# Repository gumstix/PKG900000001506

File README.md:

# Gumstix Raspberry Pi CM Robo
## PKG900000001506 ![][thumbnail]

**The Gumstix Raspberry Pi CM Robo** carrier board is a slim, computer vision-capable multimedia platform designed with miniature autonomous vehicles in mind.  The dual Raspberry Pi Camera connectors can provide either stereoscopic depth mapping for object avoidance or front- and back-facing cameras for feature identification or manual control.

I2C and UART serial connections, exposed via JST GH-style headers, can be used to connect either to PWM motor controller boards, or to a control MCU.

Instantly upgrade your project with the Gumstix Raspberry Pi CM4 Uprev board and take advantage of the CM4's increased horsepower.  Or go even further with the UprevAI and add a Google Coral TPU for lightning-fast TensorFlow processing.

__Features Include__:
* Power via **USB Type-C Power Delivery**
* Mini-HDMI-out
* DSI touch display connector
* Dual CSI2 camera connectors
* USB Type-A host connection
* 2x WS2812B-MINI RGB LEDs

__Links:__
* [AutoDoc Datasheet][autodoc]
* [Specifications][spec]
* [Store Page][store]
* [Schematics and Layout][hardware]

[thumbnail]: https://d3iwea566ns1n1.cloudfront.net/images/product/cfc476a8175b0227c75bd2853a3e6107ad4b8505.png
[autodoc]: PKG900000001506_AutoDoc.pdf
[spec]: PKG900000001506_SpecSheet.pdf
[store]: https://store.gumstix.com/cm-robo/
[hardware]: hardware/hardware.md
[firmware]: firmware/firmware.md

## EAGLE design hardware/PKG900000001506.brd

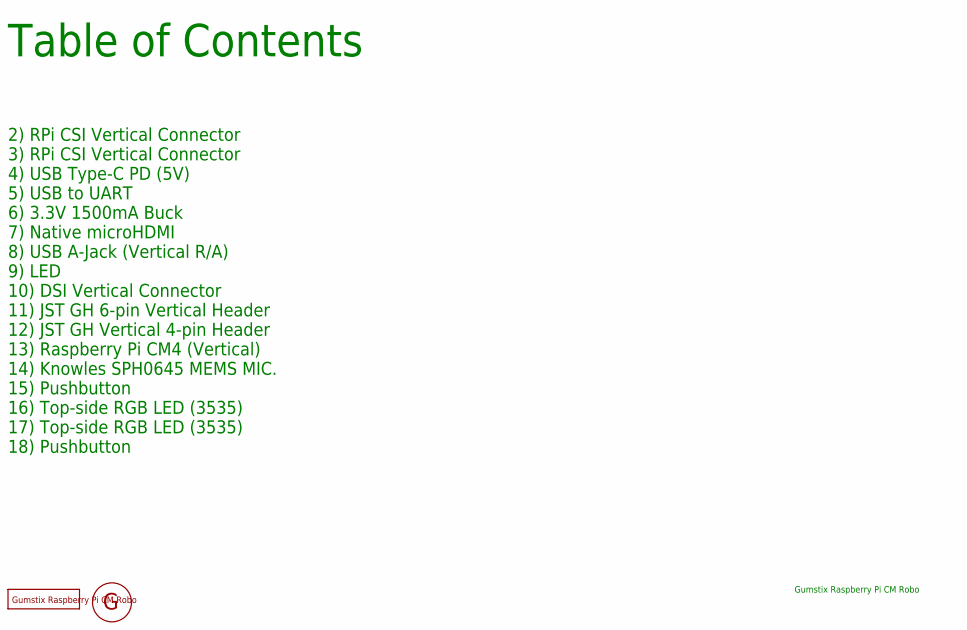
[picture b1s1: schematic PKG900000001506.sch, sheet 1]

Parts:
FD1, FD2, FD3, FD4, FD5, FD6, FD7, FD8: DNP; FIDUCIAL
U$4: DNP; GEPPETTO_LABEL
U$5: DNP; GEPPETTO_LOGO_SILK10

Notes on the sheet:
Table of Contents
Gumstix Raspberry Pi CM Robo
2) RPi CSI Vertical Connector
3) RPi CSI Vertical Connector
4) USB Type-C PD (5V)
5) USB to UART
6) 3.3V 1500mA Buck
7) Native microHDMI
8) USB A-Jack (Vertical R/A)
9) LED
10) DSI Vertical Connector
11) JST GH 6-pin Vertical Header
12) JST GH Vertical 4-pin Header
13) Raspberry Pi CM4 (Vertical)
14) Knowles SPH0645 MEMS MIC.
15) Pushbutton
16) Top-side RGB LED (3535)
17) Top-side RGB LED (3535)
18) Pushbutton

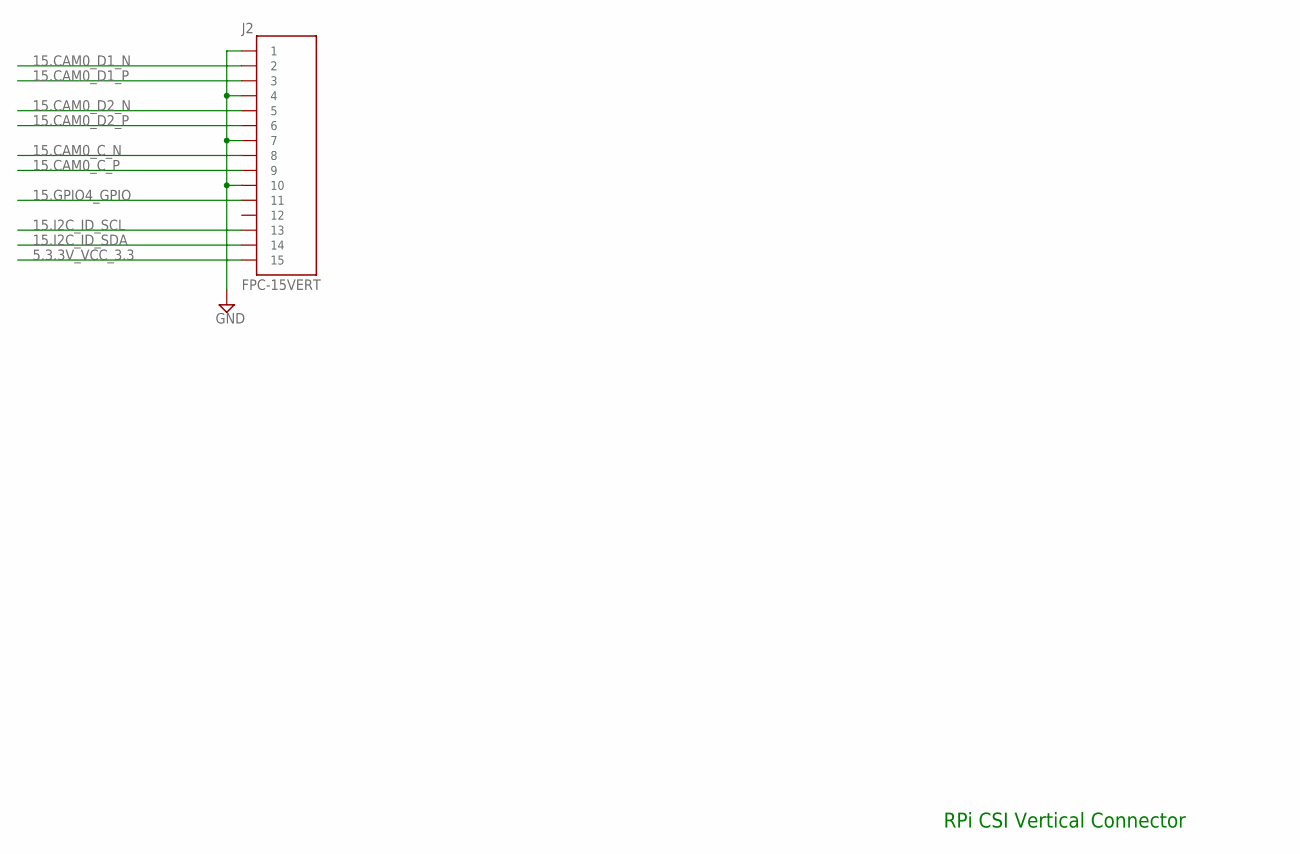
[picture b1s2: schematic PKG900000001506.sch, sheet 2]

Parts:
J2: FPC-15VERT; 1-1734248-5

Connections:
5.3.3V_VCC_3.3: J2.1_15 (15); also elsewhere on the board
15.CAM0_C_N: J2.1_8 (8); also elsewhere on the board
15.CAM0_C_P: J2.1_9 (9); also elsewhere on the board
15.CAM0_D1_N: J2.1_2 (2); also elsewhere on the board
15.CAM0_D1_P: J2.1_3 (3); also elsewhere on the board
15.CAM0_D2_N: J2.1_5 (5); also elsewhere on the board
15.CAM0_D2_P: J2.1_6 (6); also elsewhere on the board
15.GPIO4_GPIO: J2.1_11 (11); also elsewhere on the board
15.I2C_ID_SCL: J2.1_13 (13); also elsewhere on the board
15.I2C_ID_SDA: J2.1_14 (14); also elsewhere on the board
GND: J2.1_1 (1), J2.1_4 (4), J2.1_7 (7), J2.1_10 (10); also elsewhere on the board

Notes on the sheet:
RPi CSI Vertical Connector

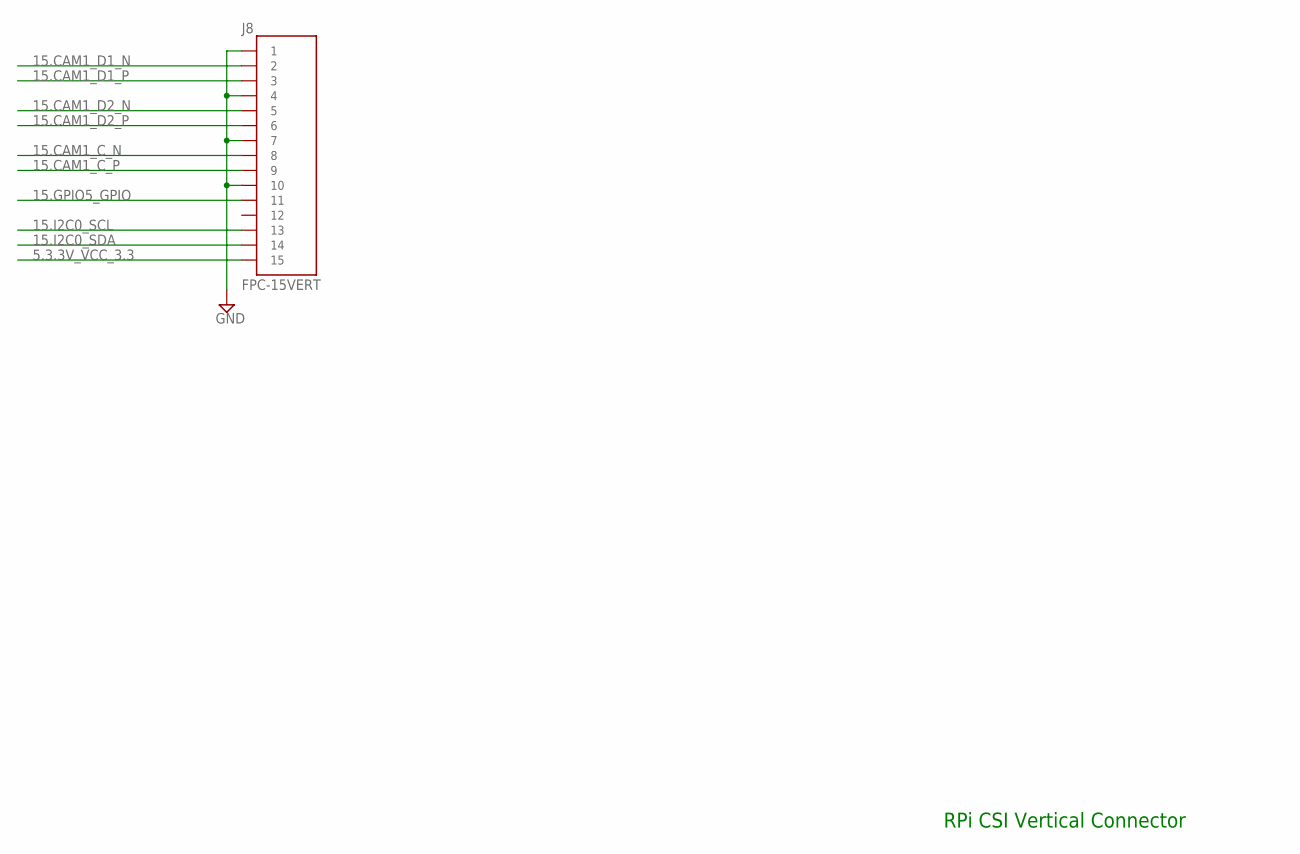
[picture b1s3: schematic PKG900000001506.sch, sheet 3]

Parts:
J8: FPC-15VERT; 1-1734248-5

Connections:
5.3.3V_VCC_3.3: J8.1_15 (15); also elsewhere on the board
15.CAM1_C_N: J8.1_8 (8); also elsewhere on the board
15.CAM1_C_P: J8.1_9 (9); also elsewhere on the board
15.CAM1_D1_N: J8.1_2 (2); also elsewhere on the board
15.CAM1_D1_P: J8.1_3 (3); also elsewhere on the board
15.CAM1_D2_N: J8.1_5 (5); also elsewhere on the board
15.CAM1_D2_P: J8.1_6 (6); also elsewhere on the board
15.GPIO5_GPIO: J8.1_11 (11); also elsewhere on the board
15.I2C0_SCL: J8.1_13 (13); also elsewhere on the board
15.I2C0_SDA: J8.1_14 (14); also elsewhere on the board
GND: J8.1_1 (1), J8.1_4 (4), J8.1_7 (7), J8.1_10 (10); also elsewhere on the board

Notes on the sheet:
RPi CSI Vertical Connector

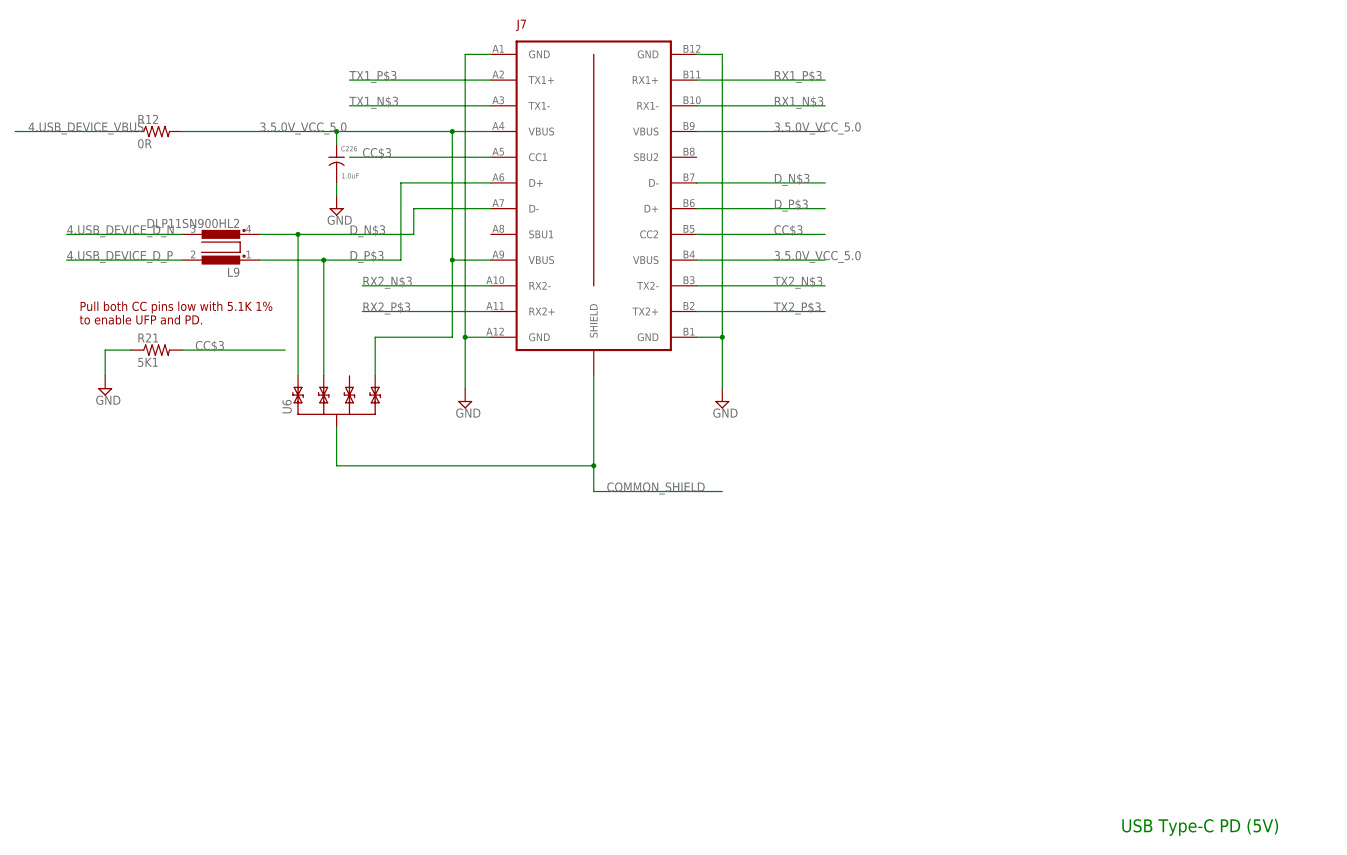
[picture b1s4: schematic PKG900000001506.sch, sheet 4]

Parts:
C226: 1.0uF; 0402
J7: USB-TYPE-C; USB-TYPE-C-SMT
L9: DLP11SN900HL2; 0504-DLP11S
R12: 0R; 0201
R21: 5K1; 0201
U6: TPD4E02B0410-USON; UFDFN-10

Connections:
3.5.0V_VCC_5.0: C226.1, J7.A4 (VBUS), J7.A9 (VBUS), J7.B4 (VBUS), J7.B9 (VBUS), R12.2, U6.5 (P4), U6.6 (P4); also elsewhere on the board
4.USB_DEVICE_D_N: L9.3; also elsewhere on the board
4.USB_DEVICE_D_P: L9.2; also elsewhere on the board
4.USB_DEVICE_VBUS: R12.1; also elsewhere on the board
CC$3: J7.A5 (CC1), J7.B5 (CC2), R21.2
COMMON_SHIELD: J7.P$1 (SHIELD), J7.P$2 (SHIELD), J7.P$3 (SHIELD), J7.P$4 (SHIELD), U6.3 (SHIELD), U6.8 (SHIELD); also elsewhere on the board
D_N$3: J7.A7 (D-), J7.B7 (D-), L9.4, U6.1, U6.10 (P1)
D_P$3: J7.A6 (D+), J7.B6 (D+), L9.1, U6.2, U6.9 (P2)
GND: C226.2, J7.A1 (GND), J7.A12 (GND), J7.B1 (GND), J7.B12 (GND), R21.1; also elsewhere on the board
RX1_N$3: J7.B10 (RX1-)
RX1_P$3: J7.B11 (RX1+)
RX2_N$3: J7.A10 (RX2-)
RX2_P$3: J7.A11 (RX2+)
TX1_N$3: J7.A3 (TX1-)
TX1_P$3: J7.A2 (TX1+)
TX2_N$3: J7.B3 (TX2-)
TX2_P$3: J7.B2 (TX2+)

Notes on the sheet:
USB Type-C PD (5V)
Pull both CC pins low with 5.1K 1% to enable UFP and PD.

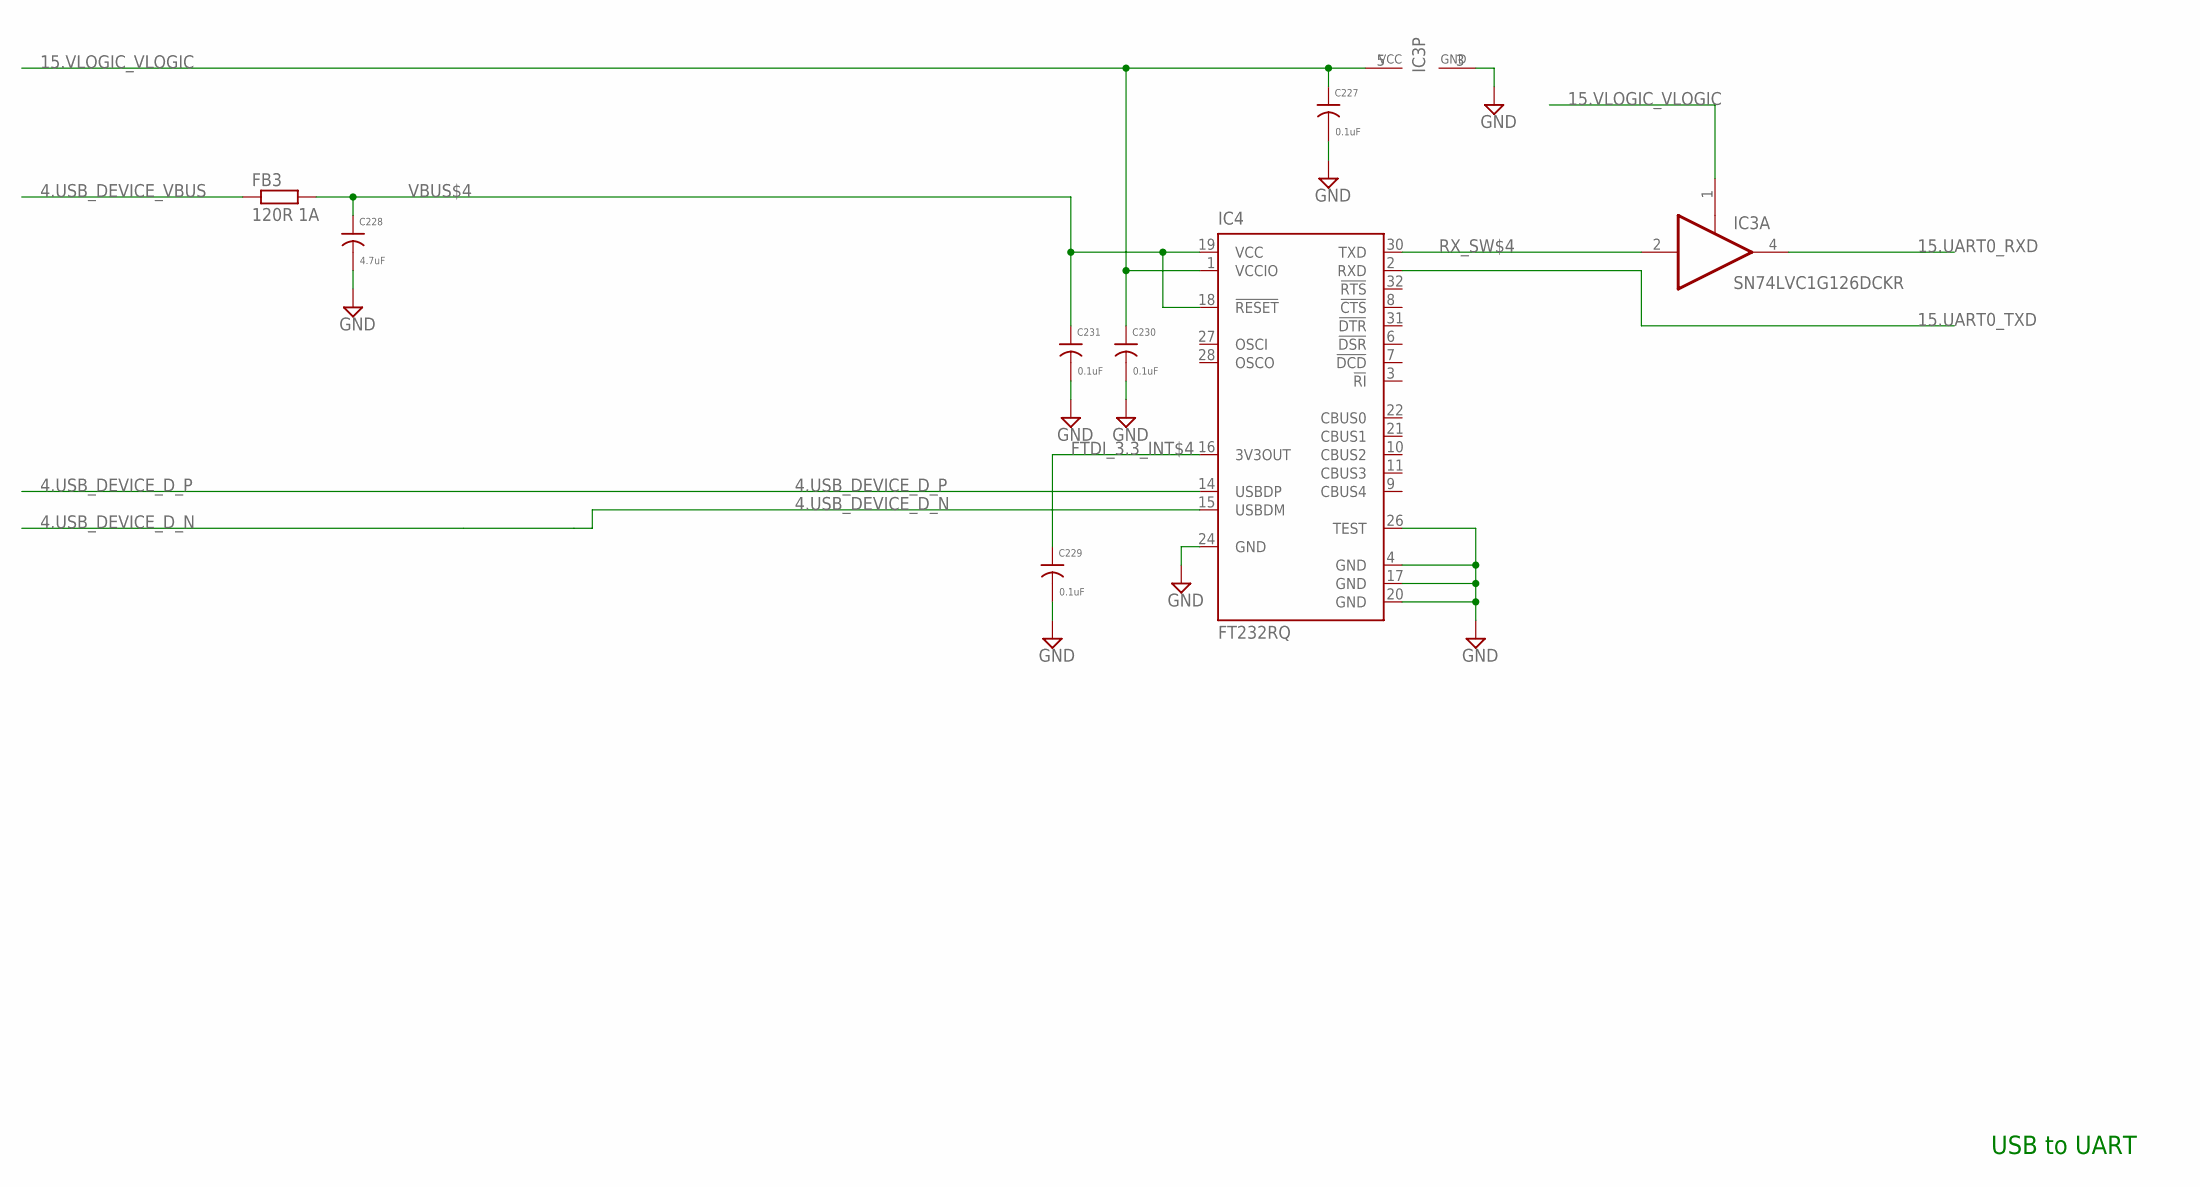
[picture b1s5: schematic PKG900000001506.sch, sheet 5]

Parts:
C227, C229, C230, C231: 0.1uF; 0201
C228: 4.7uF; 0603
FB3: 120R 1A; 0402
IC3: SN74LVC1G126DCKR; SC70-5
IC4: FT232RQ; QFN32

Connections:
4.USB_DEVICE_D_N: IC4.15 (USBDM); also elsewhere on the board
4.USB_DEVICE_D_P: IC4.14 (USBDP); also elsewhere on the board
4.USB_DEVICE_VBUS: FB3.1; also elsewhere on the board
15.UART0_RXD: IC3.4 (O); also elsewhere on the board
15.UART0_TXD: IC4.2 (RXD); also elsewhere on the board
15.VLOGIC_VLOGIC: C227.1, C230.1, IC3.1 (OE), IC3.5 (VCC), IC4.1 (VCCIO); also elsewhere on the board
FTDI_3.3_INT$4: C229.1, IC4.16 (3V3OUT)
GND: C227.2, C228.2, C229.2, C230.2, C231.2, IC3.3 (GND), IC4.4 (GND), IC4.17 (GND), IC4.20 (GND), IC4.24 (GND), IC4.26 (TEST); also elsewhere on the board
RX_SW$4: IC3.2 (I), IC4.30 (TXD)
VBUS$4: C228.1, C231.1, FB3.2, IC4.18 (!RESET), IC4.19 (VCC)

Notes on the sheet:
USB to UART

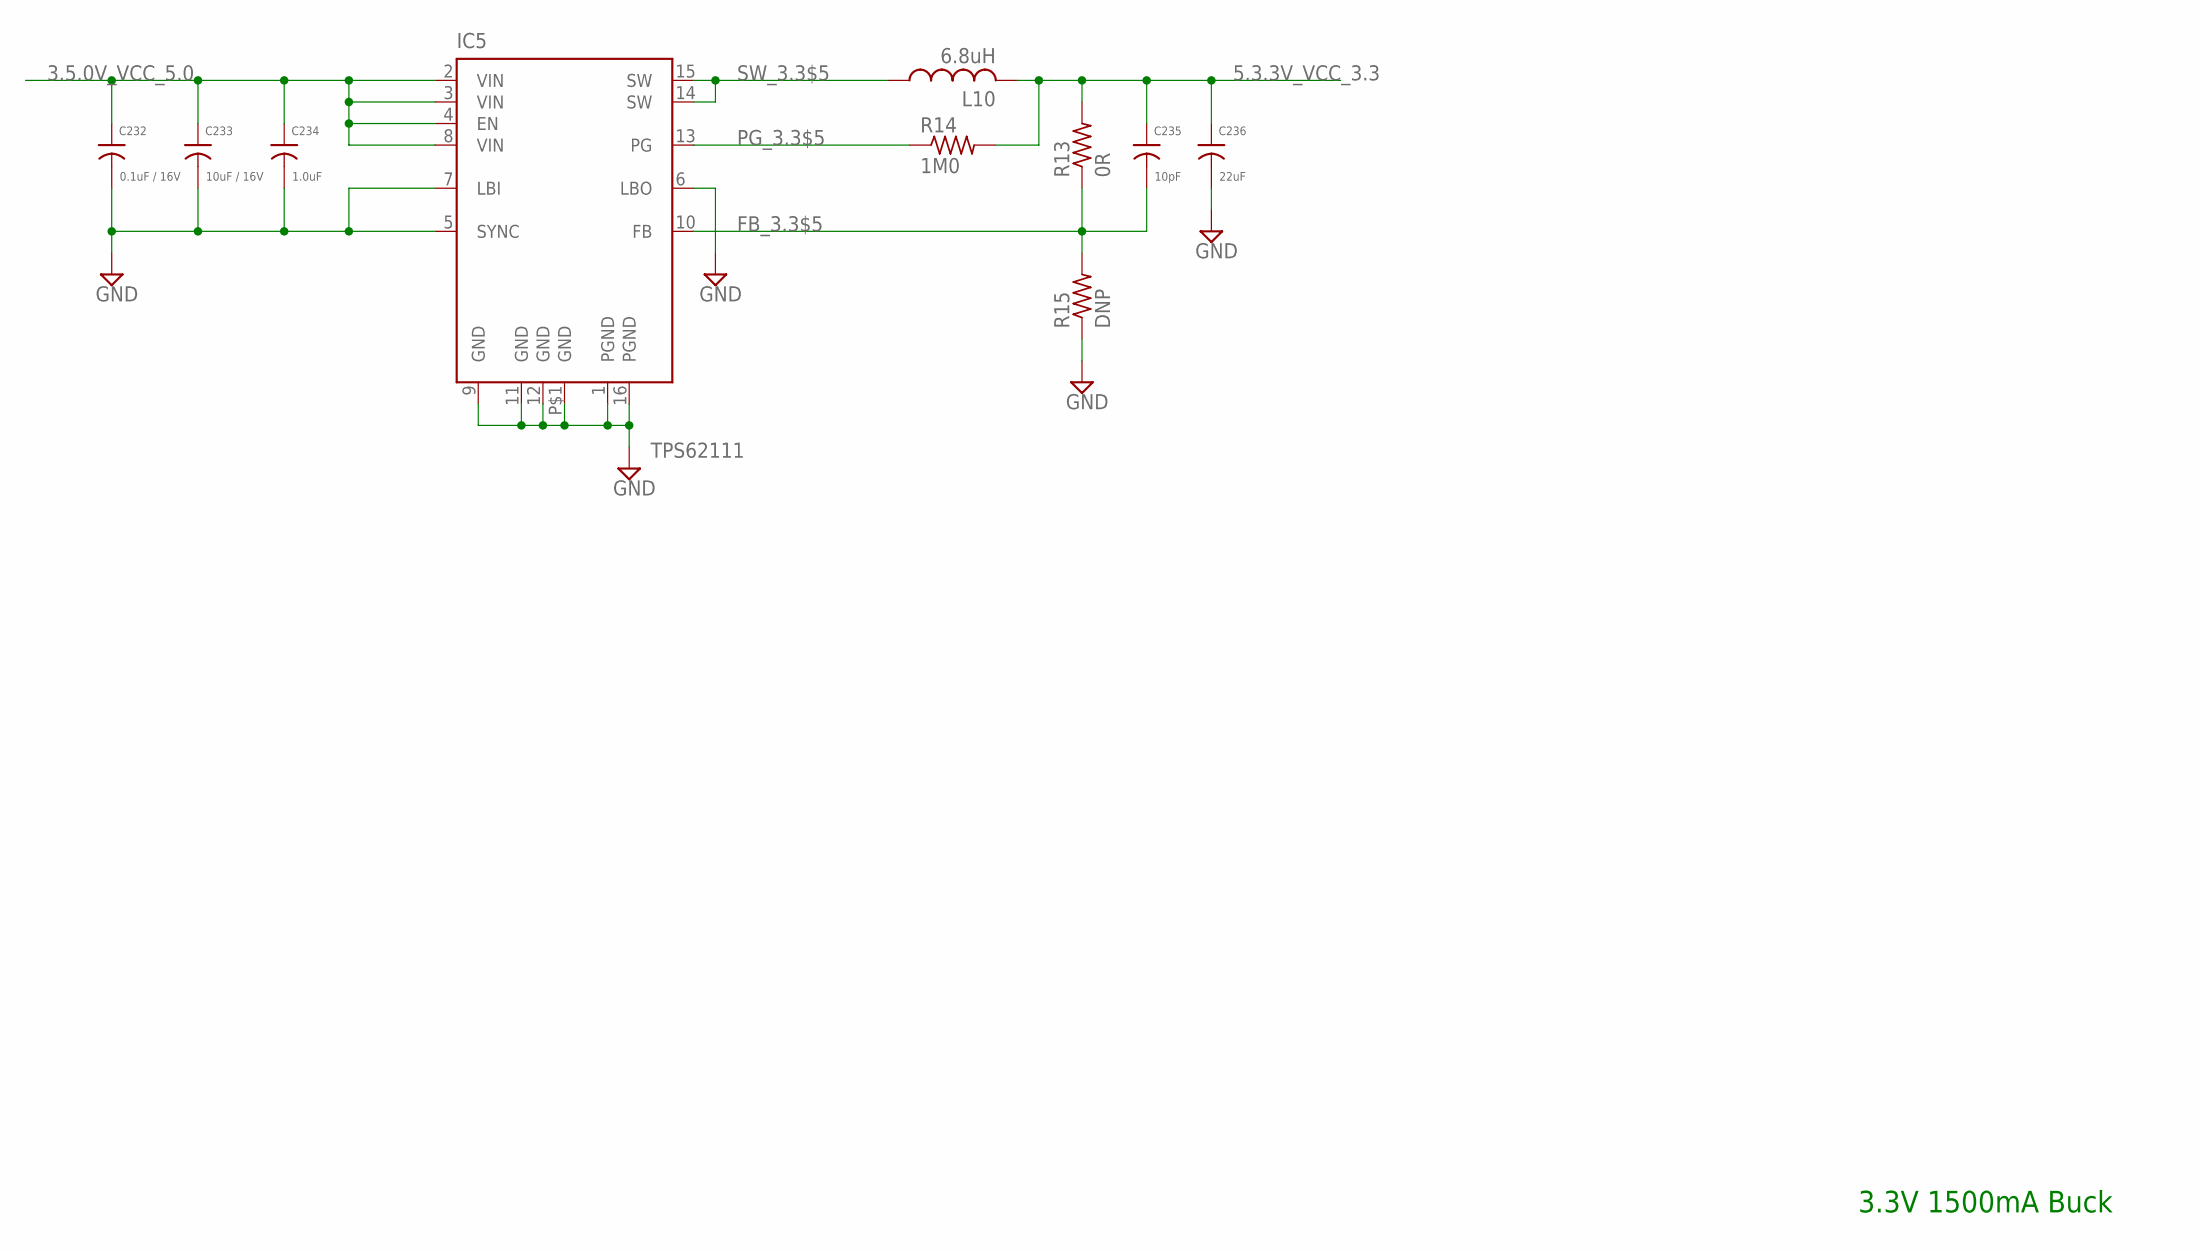
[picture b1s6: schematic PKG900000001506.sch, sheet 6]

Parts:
C232: 0.1uF / 16V; 0402
C233: 10uF / 16V; 0805
C234: 1.0uF; 0402
C235: 10pF; 0201
C236: 22uF; 0805
IC5: TPS62111; PQFP16
L10: 6.8uH; 1515
R13: 0R; 0402
R14: 1M0; 0201
R15: DNP; 0402

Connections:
3.5.0V_VCC_5.0: C232.1, C233.1, C234.1, IC5.2 (VIN), IC5.3 (VIN), IC5.4 (EN), IC5.8 (VIN); also elsewhere on the board
5.3.3V_VCC_3.3: C235.1, C236.1, L10.2, R13.2, R14.2; also elsewhere on the board
FB_3.3$5: C235.2, IC5.10 (FB), R13.1, R15.2
GND: C232.2, C233.2, C234.2, C236.2, IC5.1 (PGND), IC5.5 (SYNC), IC5.6 (LBO), IC5.7 (LBI), IC5.9 (GND), IC5.11 (GND), IC5.12 (GND), IC5.16 (PGND), IC5.P$1 (GND), R15.1; also elsewhere on the board
PG_3.3$5: IC5.13 (PG), R14.1
SW_3.3$5: IC5.14 (SW), IC5.15 (SW), L10.1

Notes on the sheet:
3.3V 1500mA Buck

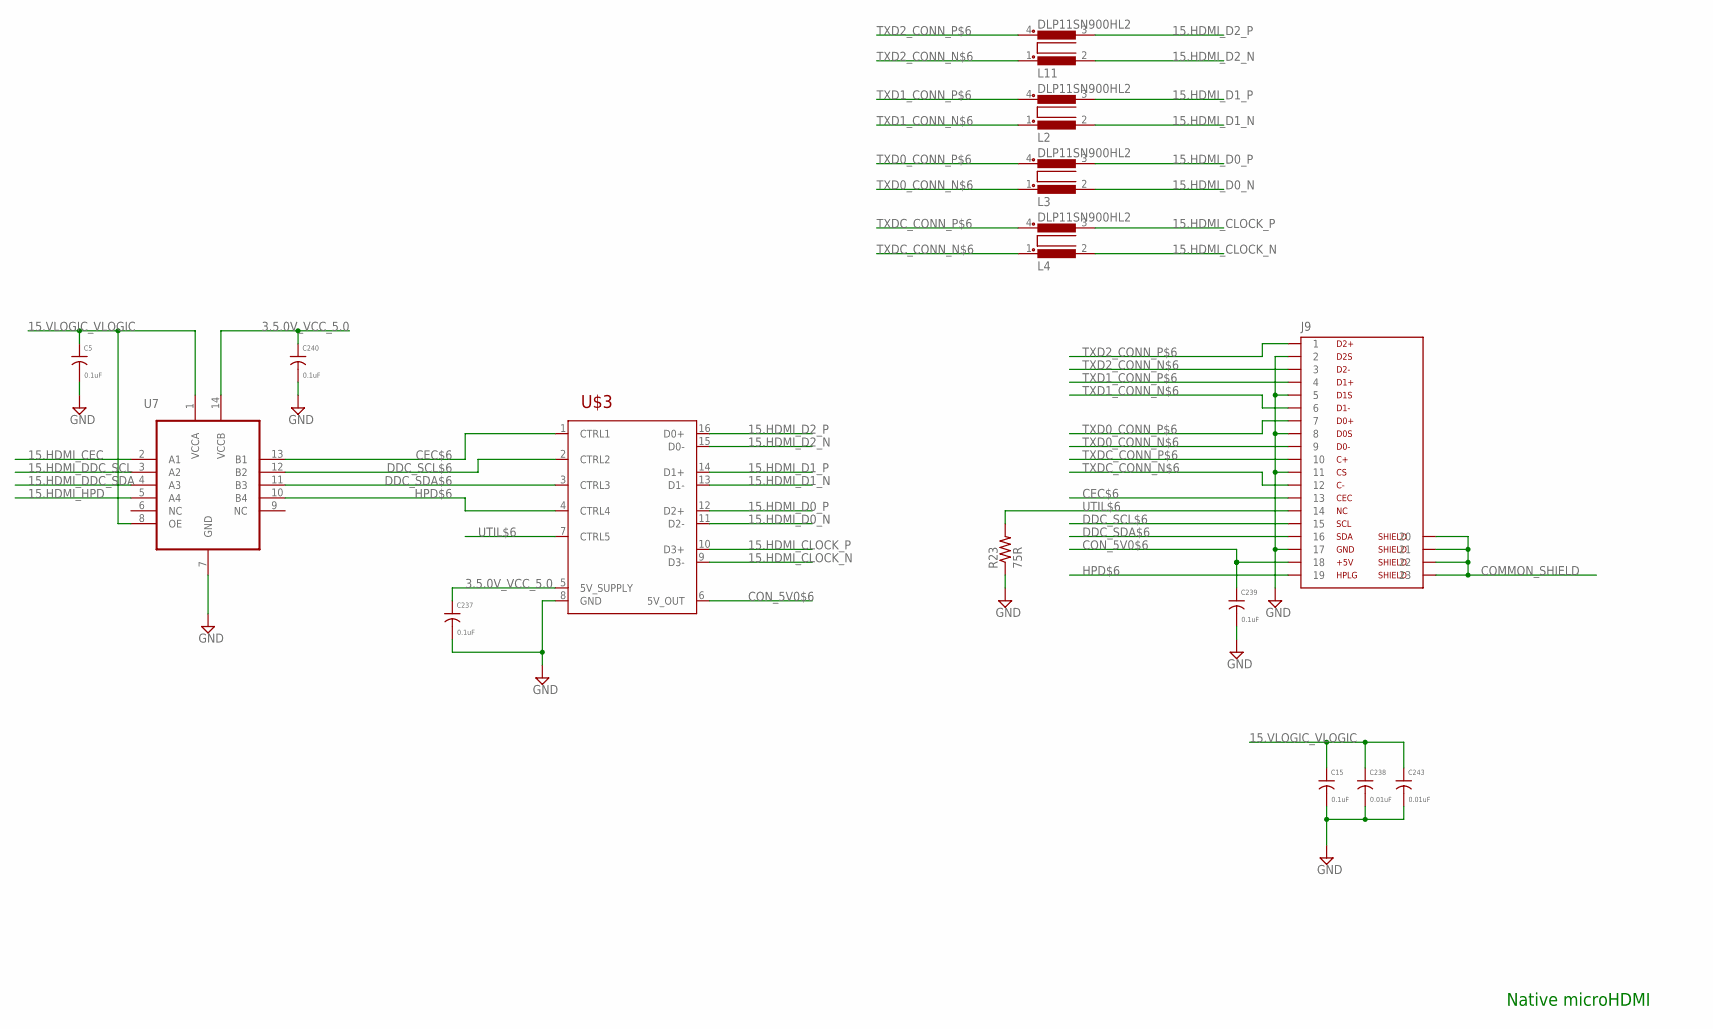
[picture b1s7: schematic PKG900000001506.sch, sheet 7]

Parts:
C5, C15, C237, C239, C240: 0.1uF; 0201
C238, C243: 0.01uF; 0201
J9: HDMIMICRO; 46765-001
L2, L3, L4, L11: DLP11SN900HL2; 0504-DLP11S
R23: 75R; 0402
U7: TXS0104E; S-PVQFN-N14
U$3: TPD13S523TSSOP; TSSOP16

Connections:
3.5.0V_VCC_5.0: C237.1, C240.1, U7.14 (VCCB), U$3.5 (5V_SUPPLY); also elsewhere on the board
15.HDMI_CEC: U7.2 (A1); also elsewhere on the board
15.HDMI_CLOCK_N: L4.2, U$3.9 (D3-); also elsewhere on the board
15.HDMI_CLOCK_P: L4.3, U$3.10 (D3+); also elsewhere on the board
15.HDMI_D0_N: L3.2, U$3.11 (D2-); also elsewhere on the board
15.HDMI_D0_P: L3.3, U$3.12 (D2+); also elsewhere on the board
15.HDMI_D1_N: L2.2, U$3.13 (D1-); also elsewhere on the board
15.HDMI_D1_P: L2.3, U$3.14 (D1+); also elsewhere on the board
15.HDMI_D2_N: L11.2, U$3.15 (D0-); also elsewhere on the board
15.HDMI_D2_P: L11.3, U$3.16 (D0+); also elsewhere on the board
15.HDMI_DDC_SCL: U7.3 (A2); also elsewhere on the board
15.HDMI_DDC_SDA: U7.4 (A3); also elsewhere on the board
15.HDMI_HPD: U7.5 (A4); also elsewhere on the board
15.VLOGIC_VLOGIC: C5.1, C15.1, C238.1, C243.1, U7.1 (VCCA), U7.8 (OE); also elsewhere on the board
CEC$6: J9.15 (13), U7.13 (B1), U$3.1 (CTRL1)
COMMON_SHIELD: J9.CON1 (20), J9.CON2 (21), J9.CON3 (22), J9.CON4 (23); also elsewhere on the board
CON_5V0$6: C239.1, J9.19 (18), U$3.6 (5V_OUT)
DDC_SCL$6: J9.17 (15), U7.12 (B2), U$3.2 (CTRL2)
DDC_SDA$6: J9.18 (16), U7.11 (B3), U$3.3 (CTRL3)
GND: C5.2, C15.2, C237.2, C238.2, C239.2, C240.2, C243.2, J9.4 (2), J9.7 (5), J9.10 (8), J9.13 (11), J9.16 (17), R23.1, U7.7 (GND), U$3.8 (GND); also elsewhere on the board
HPD$6: J9.1 (19), U7.10 (B4), U$3.4 (CTRL4)
TXD0_CONN_N$6: J9.11 (9), L3.1
TXD0_CONN_P$6: J9.9 (7), L3.4
TXD1_CONN_N$6: J9.8 (6), L2.1
TXD1_CONN_P$6: J9.6 (4), L2.4
TXD2_CONN_N$6: J9.5 (3), L11.1
TXD2_CONN_P$6: J9.3 (1), L11.4
TXDC_CONN_N$6: J9.14 (12), L4.1
TXDC_CONN_P$6: J9.12 (10), L4.4
UTIL$6: J9.2 (14), R23.2, U$3.7 (CTRL5)

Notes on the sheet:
Native microHDMI

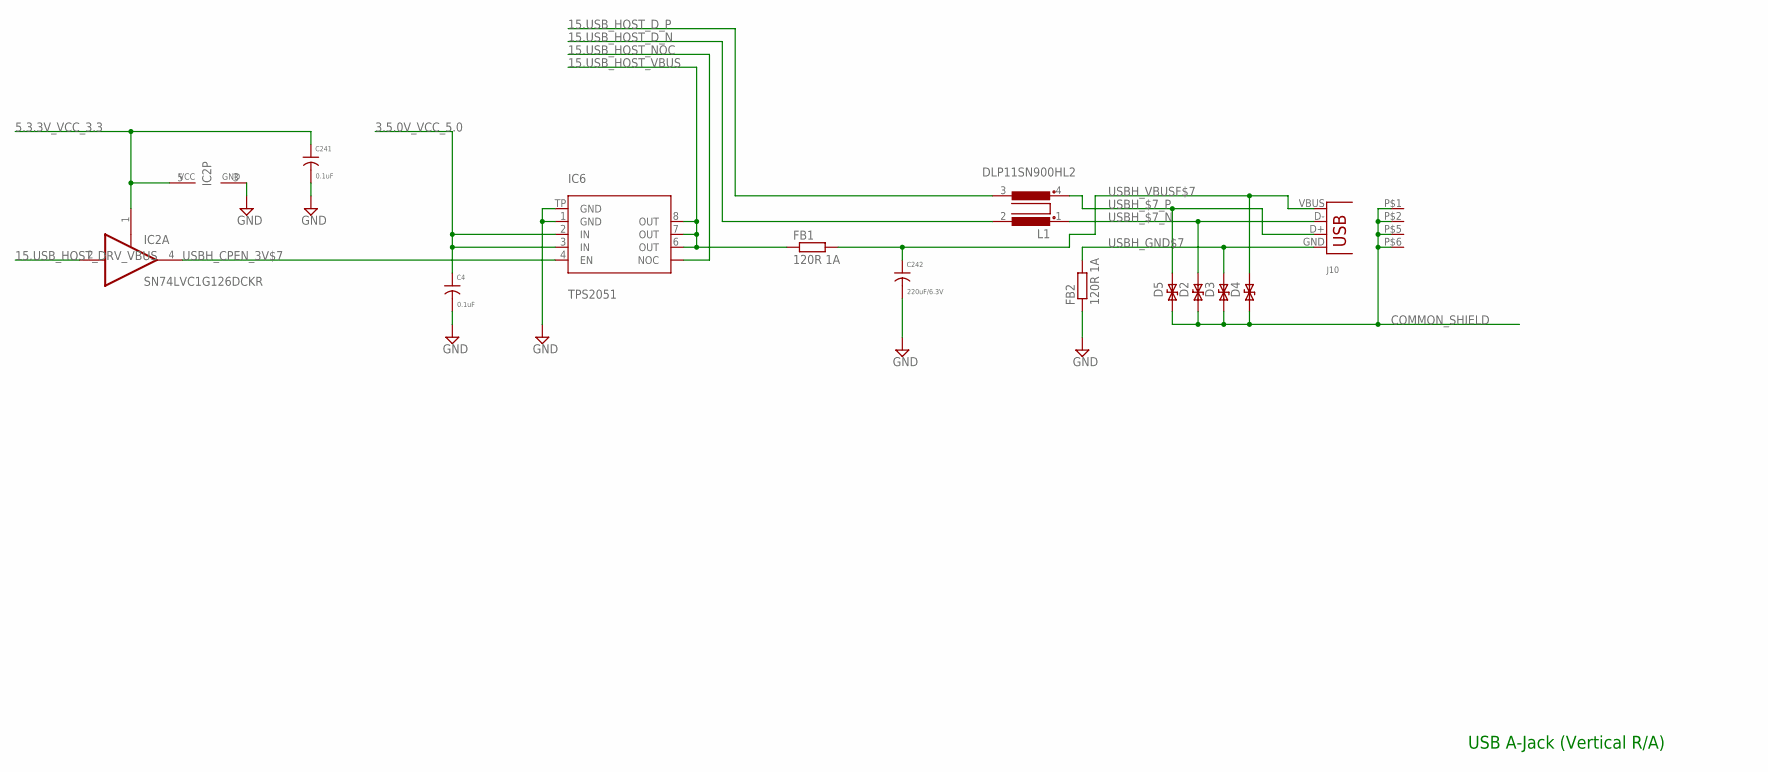
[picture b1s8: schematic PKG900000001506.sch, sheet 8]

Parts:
C4, C241: 0.1uF; 0201
C242: 220uF/6.3V; 1206
D2, D5: PS04LTVA1; D0402
D3, D4: B72590D50A060; D0402
FB1, FB2: 120R 1A; 0402
IC2: SN74LVC1G126DCKR; SC70-5
IC6: TPS2051; MSOP8-PAD
J10: USB-A-H-RA
L1: DLP11SN900HL2; 0504-DLP11S

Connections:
3.5.0V_VCC_5.0: C4.1, IC6.2 (IN), IC6.3 (IN); also elsewhere on the board
5.3.3V_VCC_3.3: C241.1, IC2.1 (OE), IC2.5 (VCC); also elsewhere on the board
15.USB_HOST_DRV_VBUS: IC2.2 (I); also elsewhere on the board
15.USB_HOST_D_N: L1.2; also elsewhere on the board
15.USB_HOST_D_P: L1.3; also elsewhere on the board
15.USB_HOST_NOC: IC6.5 (NOC)
15.USB_HOST_VBUS: FB1.1, IC6.6 (OUT), IC6.7 (OUT), IC6.8 (OUT)
COMMON_SHIELD: D2.P1, D3.P1, D4.P1, D5.P1, J10.P$1 (P1), J10.P$2 (P2), J10.P$5 (P3), J10.P$6 (P4); also elsewhere on the board
GND: C4.2, C241.2, C242.2, FB2.1, IC2.3 (GND), IC6.1 (GND), IC6.TP (GND); also elsewhere on the board
USBH_$7_N: D2.P2, J10.D-, L1.1
USBH_$7_P: D5.P2, J10.D+, L1.4
USBH_CPEN_3V$7: IC2.4 (O), IC6.4 (EN)
USBH_GND$7: D3.P2, FB2.2, J10.GND
USBH_VBUSF$7: C242.1, D4.P2, FB1.2, J10.VBUS

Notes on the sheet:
USB A-Jack (Vertical R/A)

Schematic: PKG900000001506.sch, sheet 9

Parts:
D6: GREEN; D0603
Q2: BSS138; SOT23
R24: 100K 1%; 0201
R25: 1K; 0201
R27: 600R; 0402

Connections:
5.3.3V_VCC_3.3: R27.2; also elsewhere on the board
15.SYS_EN_SYSEN: R24.2, R25.1; also elsewhere on the board
ANODE$11: D6.A, R27.1
GATE$11: Q2.1 (G), R25.2
GND: Q2.2 (S), R24.1; also elsewhere on the board
LED-$11: D6.C, Q2.3 (D)

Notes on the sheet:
LED

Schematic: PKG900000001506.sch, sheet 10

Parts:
J11: FPC-15VERT; 1-1734248-5
R16, R31: 1K5; 0201

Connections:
5.3.3V_VCC_3.3: J11.1_14 (14), J11.1_15 (15), R16.2, R31.2; also elsewhere on the board
15.DSI1_C_N: J11.1_5 (5); also elsewhere on the board
15.DSI1_C_P: J11.1_6 (6); also elsewhere on the board
15.DSI1_D1_N: J11.1_8 (8); also elsewhere on the board
15.DSI1_D1_P: J11.1_9 (9); also elsewhere on the board
15.DSI1_D2_N: J11.1_2 (2); also elsewhere on the board
15.DSI1_D2_P: J11.1_3 (3); also elsewhere on the board
15.I2C0_SCL: J11.1_11 (11), R31.1; also elsewhere on the board
15.I2C0_SDA: J11.1_12 (12), R16.1; also elsewhere on the board
GND: J11.1_1 (1), J11.1_4 (4), J11.1_7 (7), J11.1_10 (10), J11.1_13 (13); also elsewhere on the board

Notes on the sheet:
DSI Vertical Connector

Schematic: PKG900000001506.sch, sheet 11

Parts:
C3, C7: 0.1uF; 0201
J12: JST-GH-6V
R11: 10K 1%; 0201
U16, U18: TS3A5223; UQFN-10

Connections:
3.5.0V_VCC_5.0: J12.P1; also elsewhere on the board
5.3.3V_VCC_3.3: C3.1, C7.1, U16.1 (VCC), U18.1 (VCC); also elsewhere on the board
15.UART4_4W_CTS: U18.5 (NC1); also elsewhere on the board
15.UART4_4W_CTS_: J12.P4, U18.3 (COM1)
15.UART4_4W_RTS: U18.7 (NC2); also elsewhere on the board
15.UART4_4W_RTS_: J12.P5, U18.9 (COM2)
15.UART4_4W_RXD: U16.7 (NC2); also elsewhere on the board
15.UART4_4W_RXD_: J12.P3, U16.9 (COM2)
15.UART4_4W_TXD: U16.5 (NC1); also elsewhere on the board
15.UART4_4W_TXD_: J12.P2, U16.3 (COM1)
GND: C3.2, C7.2, J12.P6, R11.1, U16.6 (GND), U18.6 (GND); also elsewhere on the board
GPIO7: R11.2, U16.4 (SEL1), U16.8 (SEL2), U18.4 (SEL1), U18.8 (SEL2); also elsewhere on the board
GPIO30: U18.2 (NO1); also elsewhere on the board
GPIO31: U18.10 (NO2); also elsewhere on the board
GPIO32: U16.2 (NO1); also elsewhere on the board
GPIO33: U16.10 (NO2); also elsewhere on the board

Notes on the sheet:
JST GH 6-pin Vertical Header

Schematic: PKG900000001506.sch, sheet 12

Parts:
J1: JST-GH-4V

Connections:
3.5.0V_VCC_5.0: J1.P1; also elsewhere on the board
15.I2C1_SCL: J1.P2; also elsewhere on the board
15.I2C1_SDA: J1.P3; also elsewhere on the board
GND: J1.P4; also elsewhere on the board

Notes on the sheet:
JST GH Vertical 4-pin Header

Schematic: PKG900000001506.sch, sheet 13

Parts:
C10, C11, C12, C13: 2.2uF; 0402
C245: 0.1uF; 0201
IC1: CAT24C256YI-G; TSSOP8
Q1: BSS138; SOT23
R4: DNP; 0201
R6, R7, R8: 100K 1%; 0201
R9, R10: 1K5; 0201
R17, R20, R22: 0R; 0201
R18, R19: 10K 1%; 0201
R26: 4K7; 0201
U4: TLV751180330PDSQ; WFDFN-10
X1: DM-200P-SODIMM; DM-200P

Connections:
1V8$15: C12.1, U4.10 (OUT1), X1.183, X1.184, X1.185, X1.186
3.5.0V_VCC_5.0: C10.1, C11.1, U4.3 (EN1), U4.5 (EN2), U4.6 (IN2), U4.9 (IN1), X1.197, X1.198, X1.199, X1.200; also elsewhere on the board
3V3$15: C13.1, C245.1, IC1.8 (VCC), R8.1, R9.2, R10.2, R17.1, R18.2, U4.8 (OUT2), X1.39, X1.40, X1.41, X1.42, X1.189, X1.190, X1.191, X1.192, X1.193, X1.194
15.AUDIO_ACLKX: X1.63; also elsewhere on the board
15.AUDIO_AXR0: X1.71
15.AUDIO_AXR1: X1.69; also elsewhere on the board
15.AUDIO_FSX: X1.65; also elsewhere on the board
15.CAM0_C_N: X1.144; also elsewhere on the board
15.CAM0_C_P: X1.142; also elsewhere on the board
15.CAM0_D1_N: X1.138; also elsewhere on the board
15.CAM0_D1_P: X1.136; also elsewhere on the board
15.CAM0_D2_N: X1.150; also elsewhere on the board
15.CAM0_D2_P: X1.148; also elsewhere on the board
15.CAM1_C_N: X1.149; also elsewhere on the board
15.CAM1_C_P: X1.147; also elsewhere on the board
15.CAM1_D1_N: X1.161; also elsewhere on the board
15.CAM1_D1_P: X1.159; also elsewhere on the board
15.CAM1_D2_N: X1.155; also elsewhere on the board
15.CAM1_D2_P: X1.153; also elsewhere on the board
15.CAM1_D3_N: X1.143
15.CAM1_D3_P: X1.141
15.CAM1_D4_N: X1.137
15.CAM1_D4_P: X1.135
15.DSI1_C_N: X1.102; also elsewhere on the board
15.DSI1_C_P: X1.100; also elsewhere on the board
15.DSI1_D1_N: X1.96; also elsewhere on the board
15.DSI1_D1_P: X1.94; also elsewhere on the board
15.DSI1_D2_N: X1.120; also elsewhere on the board
15.DSI1_D2_P: X1.118; also elsewhere on the board
15.DSI1_D3_N: X1.114
15.DSI1_D3_P: X1.112
15.DSI1_D4_N: X1.108
15.DSI1_D4_P: X1.106
15.GPIO4_GPIO: X1.15; also elsewhere on the board
15.GPIO5_GPIO: X1.17; also elsewhere on the board
15.GPIO6_GPIO: X1.21; also elsewhere on the board
15.HDMI_CEC: X1.171; also elsewhere on the board
15.HDMI_CLOCK_N: X1.111; also elsewhere on the board
15.HDMI_CLOCK_P: X1.113; also elsewhere on the board
15.HDMI_D0_N: X1.117; also elsewhere on the board
15.HDMI_D0_P: X1.119; also elsewhere on the board
15.HDMI_D1_N: X1.123; also elsewhere on the board
15.HDMI_D1_P: X1.125; also elsewhere on the board
15.HDMI_D2_N: X1.129; also elsewhere on the board
15.HDMI_D2_P: X1.131; also elsewhere on the board
15.HDMI_DDC_SCL: X1.175; also elsewhere on the board
15.HDMI_DDC_SDA: X1.173; also elsewhere on the board
15.HDMI_HPD: R20.1; also elsewhere on the board
15.I2C0_SCL: X1.84; also elsewhere on the board
15.I2C0_SDA: X1.82; also elsewhere on the board
15.I2C1_SCL: IC1.6 (SCL), R10.1, X1.11; also elsewhere on the board
15.I2C1_SDA: IC1.5 (SDA), R9.1, X1.9; also elsewhere on the board
15.I2C_ID_SCL: X1.5; also elsewhere on the board
15.I2C_ID_SDA: X1.3; also elsewhere on the board
15.NRESET_NRESET: X1.177; also elsewhere on the board
15.PWM0_PWM: X1.45; also elsewhere on the board
15.SYS_EN_SYSEN: R26.1; also elsewhere on the board
15.UART0_RXD: X1.53; also elsewhere on the board
15.UART0_TXD: X1.51; also elsewhere on the board
15.UART4_4W_CTS: X1.33; also elsewhere on the board
15.UART4_4W_RTS: X1.35; also elsewhere on the board
15.UART4_4W_RXD: X1.29; also elsewhere on the board
15.UART4_4W_TXD: X1.27; also elsewhere on the board
15.USB_HOST_DRV_VBUS: R22.2; also elsewhere on the board
15.USB_HOST_D_N: X1.167; also elsewhere on the board
15.USB_HOST_D_P: X1.165; also elsewhere on the board
15.USB_HOST_OTGID: R4.2, X1.168
15.VLOGIC_VLOGIC: R17.2, R22.1, R26.2; also elsewhere on the board
!RPIBOOT$15: X1.2
A0$15: IC1.1 (A0), R8.2
A1$15: IC1.2 (A1), R7.2
A2$15: IC1.3 (A2), R6.2
GND: C10.2, C11.2, C12.2, C13.2, C245.2, IC1.4 (GND), IC1.7 (WP), Q1.2 (S), R4.1, R6.1, R7.1, R19.1, U4.2 (GND), U4.4 (GND), U4.PAD (GND), X1.1, X1.7, X1.8, X1.13, X1.14, X1.19, X1.20, X1.25, X1.26, X1.31, X1.32, X1.37, X1.38, X1.43, X1.44, X1.49, X1.50, X1.55, X1.56, X1.61, X1.62, X1.67, X1.68, X1.73, X1.74, X1.79, X1.80, X1.85, X1.86, X1.91, X1.92, X1.97, X1.98, X1.103, X1.104, X1.109, X1.110, X1.115, X1.116, X1.121, X1.122, X1.127, X1.128, X1.133, X1.134, X1.139, X1.140, X1.145, X1.146, X1.151, X1.152, X1.157, X1.158, X1.163, X1.164, X1.169, X1.170, X1.181, X1.182, X1.187, X1.188, X1.195, X1.196; also elsewhere on the board
GPIO7: X1.23; also elsewhere on the board
GPIO30: X1.34; also elsewhere on the board
GPIO31: X1.36; also elsewhere on the board
GPIO32: X1.46; also elsewhere on the board
GPIO33: X1.48; also elsewhere on the board
HDMI_HPD_N$15: Q1.3 (D), R18.1, X1.88
HPD_GATE$15: Q1.1 (G), R19.2, R20.2
PIN90$15: X1.90

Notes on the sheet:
Raspberry Pi CM4 (Vertical)
GPIOs 28-43 do not connect to BCM2711 They are connected to a TCA6416A GPIO expander Therefore they can only be used as GPIOs

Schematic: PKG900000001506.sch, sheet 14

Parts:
C2: 0.1uF; 0201
C6: 220pF; 0201
M1: SPH0645
R3: DNP; 0201
R5: 51R1; 0402
R28: 0R; 0201

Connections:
5.3.3V_VCC_3.3: C2.1, C6.1, M1.5 (VDD), R3.2; also elsewhere on the board
15.AUDIO_ACLKX: M1.4 (BCLK); also elsewhere on the board
15.AUDIO_AXR1: R5.1; also elsewhere on the board
15.AUDIO_FSX: M1.1 (WS); also elsewhere on the board
GND: C2.2, C6.2, M1.3 (GND), R28.1; also elsewhere on the board
SDI$16: M1.6 (DATA_OUT), R5.2
SELECT$16: M1.2 (SELECT), R3.1, R28.2

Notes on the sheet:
Knowles SPH0645 MEMS MIC.

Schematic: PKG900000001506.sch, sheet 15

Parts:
C247: 47pF; 0201
D7: B72590D50A060; D0402
R29: 10K 1%; 0201
R30: 150R; 0201
S3: EVQ

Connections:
15.NRESET_NRESET: C247.1, R30.2; also elsewhere on the board
15.VLOGIC_VLOGIC: R29.2; also elsewhere on the board
BTN_A$17: D7.P2, R29.1, R30.1, S3.B@2 (B')
GND: C247.2, D7.P1, S3.A@1 (A); also elsewhere on the board

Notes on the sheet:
Pushbutton

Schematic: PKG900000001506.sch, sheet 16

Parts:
U8: WS2812B-Mini-V3; WS2812B-MINI

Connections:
3.5.0V_VCC_5.0: U8.1 (VDD); also elsewhere on the board
19.DATA_OUT_DATA: U8.4 (DIN); also elsewhere on the board
DATA_OUT: U8.2 (DOUT)
GND: U8.3 (VSS); also elsewhere on the board

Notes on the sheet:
Top-side RGB LED (3535)

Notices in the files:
parts and their libraries:
qualified_1: COMPANY_AND_YEAR: Geppetto, Gumstix Inc (c) 2019
